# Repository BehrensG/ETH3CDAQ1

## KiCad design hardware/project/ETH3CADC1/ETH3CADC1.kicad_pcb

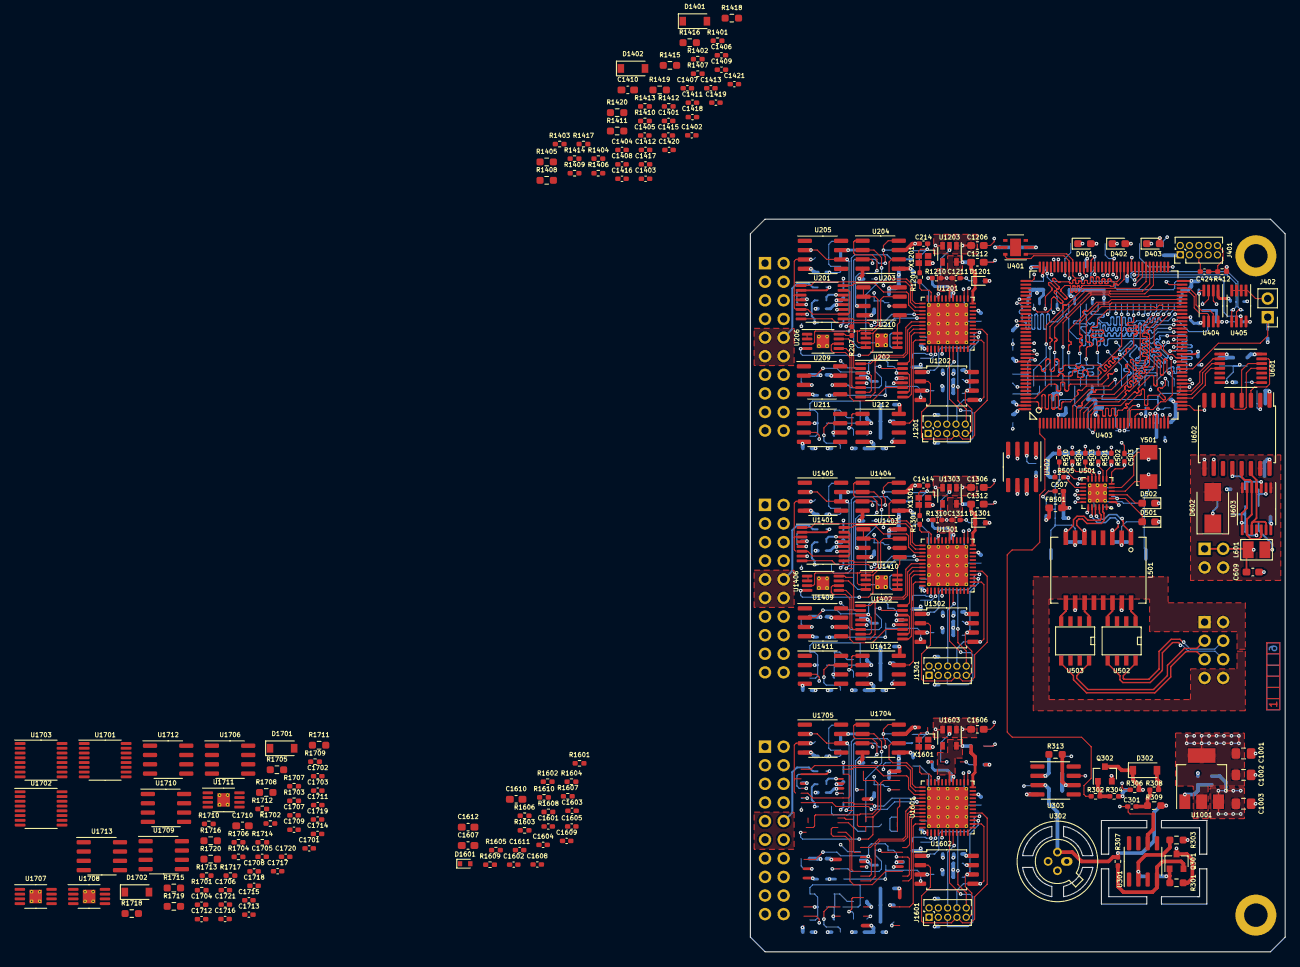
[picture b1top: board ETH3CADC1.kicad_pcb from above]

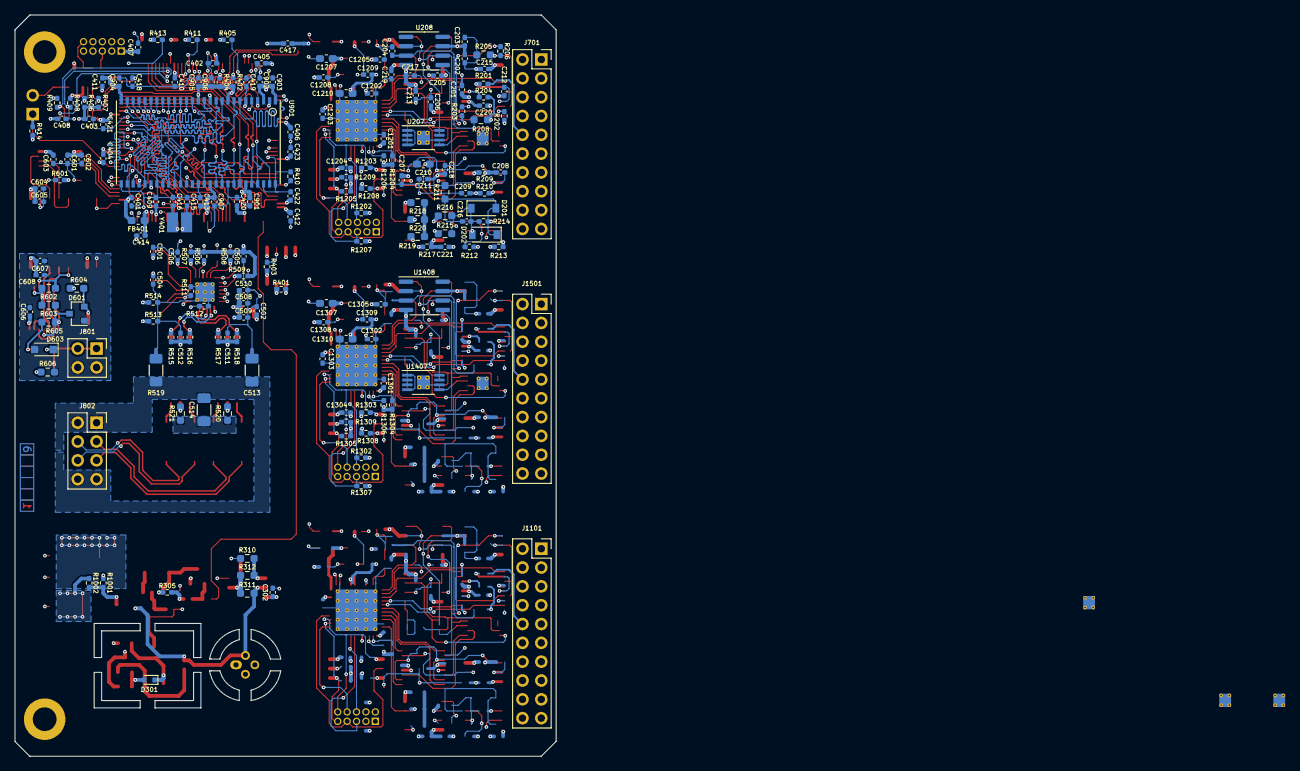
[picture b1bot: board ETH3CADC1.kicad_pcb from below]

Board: 6 copper layers, 73.0 x 100.0 mm, 408 parts (181 on the bottom side), 334 nets.

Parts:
C201, C202, C203, C204, C205, C206, C207, C208, C209, C211, C212, C213, C214, C215, C217, C218, C219, C220, C221, C301, C302, C401, C402, C403, C404, C405, C406, C407, C408, C409, C410, C411, C412, C413, C417, C421, C422, C423, C424, C502, C505, C508, C509, C510, C511, C512, C601, C603, C604, C606, C608, C901, C902, C903, C904, C905, C906, C907, C1201, C1202, C1203, C1204, C1205, C1208, C1209, C1211, C1301, C1302, C1303, C1304, C1305, C1308, C1309, C1311, C1401, C1402, C1403, C1404, C1405, C1406, C1407, C1408, C1409, C1411, C1412, C1413, C1414, C1415, C1417, C1418, C1419, C1420, C1421, C1601, C1602, C1603, C1604, C1605, C1608, C1609, C1611, C1701, C1702, C1703, C1704, C1705, C1706, C1707, C1708, C1709, C1711, C1712, C1713, C1714, C1715, C1717, C1718, C1719, C1720, C1721: 100n; C_0402_1005Metric_Pad0.74x0.62mm_HandSolder
C210, C1410, C1710: 2n2/SMD; C_0603_1608Metric_Pad1.08x0.95mm_HandSolder
C216, C1416, C1716: 33p; C_0402_1005Metric_Pad0.74x0.62mm_HandSolder
C414, C420, C506, C507, C602, C605, C607: 1u; C_0402_1005Metric_Pad0.74x0.62mm_HandSolder
C415, C416, C501, C504: 8p; C_0402_1005Metric_Pad0.74x0.62mm_HandSolder
C418, C419: 2u2; C_0402_1005Metric_Pad0.74x0.62mm_HandSolder
C503: 470p; C_0402_1005Metric_Pad0.74x0.62mm_HandSolder
C513, C514: 1n/1kV; C_1206_3216Metric_Pad1.33x1.80mm_HandSolder
C609: 47p; C_0603_1608Metric_Pad1.08x0.95mm_HandSolder
C1001: 10u/50V; C_0805_2012Metric_Pad1.18x1.45mm_HandSolder
C1002, C1003: 4u7/50V; C_0805_2012Metric_Pad1.18x1.45mm_HandSolder
C1206, C1207, C1210, C1212, C1306, C1307, C1310, C1312, C1606, C1607, C1610, C1612: 4u7; C_0603_1608Metric_Pad1.08x0.95mm_HandSolder
D201, D202, D302, D1401, D1402, D1701, D1702: BAV21W; D_SOD-123
D301: BZT585B15TQ-13; D_SOD-523
D401: BLUE; LED_0603_1608Metric_Pad1.05x0.95mm_HandSolder
D402, D502: GREEN; LED_0603_1608Metric_Pad1.05x0.95mm_HandSolder
D403: RED; LED_0603_1608Metric_Pad1.05x0.95mm_HandSolder
D501: YELLOW; LED_0603_1608Metric_Pad1.05x0.95mm_HandSolder
D601: BAV99; SOT-23
D602: SMBJ5.0A; D_SMB
D603: SD36C-01FTG; D_SOD-323_HandSoldering
D1201, D1301, D1601: CDBU0520; D_SOD-523
FB401, FB501: 742792031; L_0603_1608Metric_Pad1.05x0.95mm_HandSolder
H101, H102: MountingHole; MountingHole_3.2mm_M3_DIN965_Pad
J401: 20021111-00010T4LF; PinHeader_2x05_P1.27mm_Vertical
J402: Conn_02x01; PinHeader_1x02_P2.54mm_Vertical
J701, J1101, J1501: Conn_02x10_Odd_Even; PinSocket_2x10_P2.54mm_Vertical
J801: Conn_02x02_Odd_Even; PinSocket_2x02_P2.54mm_Vertical
J802: Conn_02x04_Odd_Even; PinSocket_2x04_P2.54mm_Vertical
J1201, J1301, J1601: Conn_02x05_Odd_Even; PinHeader_2x05_P1.27mm_Vertical
L501: 749010012A
L601: CW252016-R33G; CW252016
Q301: MMBTA55; SOT-23
Q302: BC847; SOT-23
R201, R202, R203, R204, R207, R410, R412, R414, R503, R506, R507, R508, R509, R511, R601, R1202, R1203, R1204, R1205, R1207, R1208, R1209, R1302, R1303, R1305, R1306, R1307, R1308, R1309, R1401, R1402, R1403, R1404, R1407, R1602, R1603, R1604, R1605, R1606, R1607, R1608, R1609, R1701, R1702, R1703, R1704, R1707: 10k; R_0402_1005Metric_Pad0.72x0.64mm_HandSolder
R205, R1405, R1705: 10M; R_0603_1608Metric_Pad0.98x0.95mm_HandSolder
R206, R305, R307, R1406, R1706: 0; R_0402_1005Metric_Pad0.72x0.64mm_HandSolder
R208, R218, R309, R1408, R1418, R1708, R1718: 62/.1%; R_0603_1608Metric_Pad0.98x0.95mm_HandSolder
R209, R210, R212, R213, R217, R1409, R1410, R1412, R1413, R1417, R1709, R1710, R1712, R1713, R1717: 10; R_0402_1005Metric_Pad0.72x0.64mm_HandSolder
R211, R1411, R1711: 12k/.05%; R_0603_1608Metric_Pad0.98x0.95mm_HandSolder
R214, R1414, R1714: 62k; R_0402_1005Metric_Pad0.72x0.64mm_HandSolder
R215, R1415, R1715: 620/.05%; R_0603_1608Metric_Pad0.98x0.95mm_HandSolder
R216, R220, R1416, R1420, R1716, R1720: 3k9/.05%; R_0603_1608Metric_Pad0.98x0.95mm_HandSolder
R219, R1419, R1719: 39k/.05%; R_0603_1608Metric_Pad0.98x0.95mm_HandSolder
R301, R303: 4k7/.1%; R_0603_1608Metric_Pad0.98x0.95mm_HandSolder
R302, R306: 120k; R_0402_1005Metric_Pad0.72x0.64mm_HandSolder
R304: 620k; R_0402_1005Metric_Pad0.72x0.64mm_HandSolder
R308: 12k; R_0402_1005Metric_Pad0.72x0.64mm_HandSolder
R310: 6k95/.05%; R_0603_1608Metric_Pad0.98x0.95mm_HandSolder
R311, R312: 3k01/.1%; R_0603_1608Metric_Pad0.98x0.95mm_HandSolder
R313: 0; R_0603_1608Metric_Pad0.98x0.95mm_HandSolder
R401, R1002: 120; R_0402_1005Metric_Pad0.72x0.64mm_HandSolder
R402, R404, R406, R407, R408, R409: 4k7; R_0402_1005Metric_Pad0.72x0.64mm_HandSolder
R403: 1k; R_0402_1005Metric_Pad0.72x0.64mm_HandSolder
R405, R413: 680; R_0402_1005Metric_Pad0.72x0.64mm_HandSolder
R411: 560; R_0402_1005Metric_Pad0.72x0.64mm_HandSolder
R501, R502, R504, R505: 33; R_0402_1005Metric_Pad0.72x0.64mm_HandSolder
R510: 1k5; R_0402_1005Metric_Pad0.72x0.64mm_HandSolder
R512: 12k1; R_0402_1005Metric_Pad0.72x0.64mm_HandSolder
R513, R514: 270; R_0402_1005Metric_Pad0.72x0.64mm_HandSolder
R515, R516, R517, R518: 49R9; R_0402_1005Metric_Pad0.72x0.64mm_HandSolder
R519: 1M/1kV; R_1206_3216Metric_Pad1.30x1.75mm_HandSolder
R520, R521: 75/1%; R_0603_1608Metric_Pad0.98x0.95mm_HandSolder
R602: 14k7; R_0603_1608Metric_Pad0.98x0.95mm_HandSolder
R603: 100; R_0603_1608Metric_Pad0.98x0.95mm_HandSolder
R604: 1k; R_0603_1608Metric_Pad0.98x0.95mm_HandSolder
R605: 47; R_0603_1608Metric_Pad0.98x0.95mm_HandSolder
R606: 51R1; R_0603_1608Metric_Pad0.98x0.95mm_HandSolder
R1001: 1k23; R_0402_1005Metric_Pad0.72x0.64mm_HandSolder
R1201, R1301, R1601: 22; R_0402_1005Metric_Pad0.72x0.64mm_HandSolder
R1206, R1304: NC; R_0402_1005Metric_Pad0.72x0.64mm_HandSolder
R1210, R1310, R1610: 100; R_0402_1005Metric_Pad0.72x0.64mm_HandSolder
U201, U1401, U1701, U1703: DG211; TSSOP-16_4.4x5mm_P0.65mm
U202, U1402, U1702: DG211B; TSSOP-16_4.4x5mm_P0.65mm
U203, U1403, U1704: OPA2192; SOIC-8_3.9x4.9mm_P1.27mm
U204, U1404, U1705: DG419DY; SOIC-8_3.9x4.9mm_P1.27mm
U205, U209, U1405, U1409, U1706, U1710: OPA140; SOIC-8_3.9x4.9mm_P1.27mm
U206, U1406, U1707: LT5400-100k-100k; MSOP-8-1EP_3x3mm_P0.65mm_EP1.73x1.85mm_ThermalVias
U207, U1407, U1708: LT5400-5k-1k; MSOP-8-1EP_3x3mm_P0.65mm_EP1.73x1.85mm_ThermalVias
U208, U303, U1408, U1709: OPA177; SOIC-8_3.9x4.9mm_P1.27mm
U210, U1410, U1711: LT5400-10k-10k; MSOP-8-1EP_3x3mm_P0.65mm_EP1.73x1.85mm_ThermalVias
U211, U1411, U1712: OPA192; SOIC-8_3.9x4.9mm_P1.27mm
U212, U1412, U1713: LM311; SOIC-8_3.9x4.9mm_P1.27mm
U301: LT1021-7; SOIC-8_3.9x4.9mm_P1.27mm
U302: LM399H; LMx99
U401: HDC1080; Texas_PWSON-N6
U402: MCP2551-I-SN; SOIC-8_3.9x4.9mm_P1.27mm
U403: STM32H743ZI; TQFP-144_20x20mm_P0.5mm
U404: PCA9517; MSOP-8_3x3mm_P0.65mm
U405: 24LC08B-E/MS; MSOP-8_3x3mm_P0.65mm
U501: LAN8742A; QFN-24-1EP_4x4mm_P0.5mm_EP2.6x2.6mm_ThermalVias
U502, U503: LC03-3.3; SO8E
U601: TXB0104PW; TSSOP-14_4.4x5mm_P0.65mm
U602: ADuM5402; SOIC-16W_7.5x10.3mm_P1.27mm
U603: 74AC125; TSSOP-14_4.4x5mm_P0.65mm
U901: MT48LC16M16A2P-6A; TSSOP-54
U1001: LM337_SOT223; SOT-223-3_TabPin2
U1201, U1301, U1601: ICE40UP5K-SG48ITR; QFN-48-1EP_7x7mm_P0.5mm_EP5.6x5.6mm_ThermalVias
U1202, U1302, U1602: W25Q32JVSS; SOIC-8_5.23x5.23mm_P1.27mm
U1203, U1303, U1603: AP2127K-1.2; SOT-23-5
X1201, X1301, X1601: ASAAIG-40.000MHZ; ASAAIG
Y401: NX3225GD-8MHZ; NX3225GD
Y501: NX5032GA-25.000M-LN-CD-1; NX5032GA

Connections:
+3.3VF: C219.1, C220.1, C221.1, C401.1, C402.1, C403.1, C404.1, C405.1, C406.1, C407.1, C408.1, C409.1, C410.1, C411.1, C412.1, C413.1, C417.1, C420.1, C421.1, C422.1, C423.1, C502.1, C505.1, C601.1, C602.1, C901.1, C902.1, C903.1, C904.1, C905.1, C906.1, C907.1, C1201.1, C1202.1, C1203.1, C1204.1, C1205.1, C1206.1, C1208.1, C1301.1, C1302.1, C1303.1, C1304.1, C1305.1, C1306.1, C1308.1, C1419.1, C1420.1, C1421.1, C1601.1, C1602.1, C1603.1, C1604.1, C1605.1, C1606.1, C1608.1, C1719.1, C1720.1, C1721.1, D401.2, D402.2, D403.2, D1201.2, D1301.2, D1601.2, FB401.2, FB501.2, J401.1, J701.15, J701.16, J1101.15, J1101.16, J1501.15, J1501.16, R218.1, R402.1, R404.1, R406.1, R407.1, R408.1, R409.1, R412.1, R414.2, R506.1, R507.1, R508.1, R509.1, R510.1, R601.1, R1202.1, R1203.1, R1204.1, R1205.1, R1206.1, R1207.1, R1208.1, R1209.1, R1302.1, R1303.1, R1304.1, R1305.1, R1306.1, R1307.1, R1308.1, R1309.1, R1418.1, R1602.1, R1603.1, R1604.1, R1605.1, R1606.1, R1607.1, R1608.1, R1609.1, R1718.1, U201.12, U202.12, U204.5, U212.8, U401.5, U403.6, U403.17, U403.30, U403.39, U403.52, U403.62, U403.72, U403.84, U403.95, U403.108, U403.121, U403.131, U403.143, U403.144, U404.1, U404.5, U404.8, U405.8, U501.9, U601.1, U901.1, U901.3, U901.9, U901.14, U901.27, U901.43, U901.49, U1201.1, U1201.22, U1201.33, U1202.8, U1203.1, U1203.3, U1301.1, U1301.22, U1301.33, U1302.8, U1303.1, U1303.3, U1401.12, U1402.12, U1404.5, U1412.8, U1601.1, U1601.22, U1601.33, U1602.8, U1603.1, U1603.3, U1701.12, U1702.12, U1705.5, U1713.8, X1201.4, X1301.4, X1601.4
+5V: C603.1, C604.1, C605.1, J701.18, J1101.18, J1501.18, U402.3, U601.14, U602.1
+5V_TRIG: C606.1, C607.1, C608.1, R604.1, U602.10, U602.16, U603.14
+10VRF: R203.2, R313.1, R1403.2, R1703.2
+18VF: C201.1, C202.1, C203.1, C205.1, C206.1, C207.1, C208.1, C1401.1, C1402.1, C1403.1, C1405.1, C1406.1, C1407.1, C1408.1, C1701.1, C1702.1, C1703.1, C1705.1, C1706.1, C1707.1, C1708.1, J701.20, J1101.20, J1501.20, R209.1, R212.1, R303.1, R1409.1, R1412.1, R1709.1, R1712.1, U201.13, U202.13, U203.4, U204.4, U205.7, U208.7, U302.3, U1401.13, U1402.13, U1403.4, U1404.4, U1405.7, U1408.7, U1701.13, U1702.13, U1704.4, U1705.4, U1706.7, U1709.7
-14VF: C209.1, C211.1, C212.1, C213.1, C214.1, C215.1, C217.1, C218.1, C302.2, C1003.1, C1409.1, C1411.1, C1412.1, C1413.1, C1414.1, C1415.1, C1417.1, C1418.1, C1709.1, C1711.1, C1712.1, C1713.1, C1714.1, C1715.1, C1717.1, C1718.1, Q301.3, Q302.2, R210.2, R213.2, R217.2, R301.2, R304.2, R305.1, R1002.1, R1410.2, R1413.2, R1417.2, R1710.2, R1713.2, R1717.2, U201.4, U202.4, U203.8, U204.7, U205.4, U208.4, U303.4, U1001.3, U1401.4, U1402.4, U1403.8, U1404.7, U1405.4, U1408.4, U1701.4, U1702.4, U1704.8, U1705.7, U1706.4, U1709.4
-18VF: C1001.1, C1002.1, J701.19, J1101.19, J1501.19, U302.4, U1001.2
/ADC 1/ADIN1: J701.9, J701.10, J701.11, J701.12, R201.2
/ADC 1/FGPA1_AD_ID: U202.16, U1201.44
/ADC 1/FGPA1_AD_IIN: U202.1, U1201.42
/ADC 1/FGPA1_AD_IRN: U202.8, U1201.43
/ADC 1/FGPA1_AD_IRP: U202.9, U1201.45
/ADC 1/FPGA1_MUX_ADIN: U201.1, U1201.38
/ADC 1/FPGA1_MUX_GND: U201.8, U1201.41
/ADC 1/FPGA1_MUX_N7V: U201.16, U1201.39
/ADC 1/FPGA1_MUX_P10V: U201.9, U1201.40
/ADC 1/VREF+: U203.7, U206.4, U210.1, U210.2
/ADC 1/VREF-: U203.1, U203.2, U206.3, U210.3, U210.4
/ADC 1/VREF_N7V_LPF: C301.1, R204.2, R208.2, R308.1, R309.1, R1404.2, R1408.2, R1704.2, R1708.2
/ADC 2/ADIN2: J1501.9, J1501.10, J1501.11, J1501.12, R1401.2
/ADC 2/FGPA2_AD_ID: U1301.44, U1402.16
/ADC 2/FGPA2_AD_IIN: U1301.42, U1402.1
/ADC 2/FGPA2_AD_IRN: U1301.43, U1402.8
/ADC 2/FGPA2_AD_IRP: U1301.45, U1402.9
/ADC 2/FPGA2_MUX_ADIN: U1301.38, U1401.1
/ADC 2/FPGA2_MUX_GND: U1301.41, U1401.8
/ADC 2/FPGA2_MUX_N7V: U1301.39, U1401.16
/ADC 2/FPGA2_MUX_P10V: U1301.40, U1401.9
/ADC 2/VREF+: U1403.7, U1406.4, U1410.1, U1410.2
/ADC 2/VREF-: U1403.1, U1403.2, U1406.3, U1410.3, U1410.4
/ADC 3/ADIN3: J1101.9, J1101.10, J1101.11, J1101.12, R1701.2
/ADC 3/FGPA3_AD_ID: U1601.44, U1702.16
/ADC 3/FGPA3_AD_IIN: U1601.42, U1702.1
/ADC 3/FGPA3_AD_IRN: U1601.43, U1702.8
/ADC 3/FGPA3_AD_IRP: U1601.45, U1702.9
/ADC 3/FPGA3_MUX_ADIN: U1601.38, U1703.1
/ADC 3/FPGA3_MUX_GND: U1601.41, U1703.8
/ADC 3/FPGA3_MUX_N7V: U1601.39, U1703.16
/ADC 3/FPGA3_MUX_P10V: U1601.40, U1703.9
/ADC 3/VREF+: U1704.7, U1707.4, U1711.1, U1711.2
/ADC 3/VREF-: U1704.1, U1704.2, U1707.3, U1711.3, U1711.4
/CH1 Connector/CANH: J701.5, J1101.5, J1501.5, R401.1, U402.7
/CH1 Connector/CANL: J701.6, J1101.6, J1501.6, R401.2, U402.6
/CH1 Connector/I2C_SCL: J701.2, J1101.2, J1501.2, R406.2, U404.2
/CH1 Connector/I2C_SDA: J701.4, J1101.4, J1501.4, R407.2, U404.3
/Connector/EXT_TRIG: C609.1, D603.1, J801.1, J801.2, L601.1
/Connector/RX+: J802.3, U503.8
/Connector/RX-: J802.5, U503.5
/Connector/TX+: J802.4, U502.8
/Connector/TX-: J802.6, U502.5
/Ethernet/ETH_RXN: L501.8, R518.2, U501.22
/Ethernet/ETH_RXP: L501.6, R517.2, U501.23
/Ethernet/ETH_TXN: L501.3, R516.2, U501.20
/Ethernet/ETH_TXP: L501.1, R515.2, U501.21
/Ethernet/MODE0: R501.1, R506.2, U501.8
/Ethernet/MODE1: R502.1, R507.2, U501.7
/Ethernet/MODE2: R504.1, R508.2, U501.11
/Ethernet/NRST: C424.1, J401.10, R412.2, U403.25, U501.15
/Ethernet/REFCLK0: R505.1, R509.2, U501.14
/Ethernet/REF_CLK: R505.2, U403.35
/Ethernet/RMII_CRS_DV: R504.2, U403.43
/Ethernet/RMII_MDC: U403.27, U501.13
/Ethernet/RMII_MDIO: R510.2, U403.36, U501.12
/Ethernet/RMII_RXD0: R501.2, U403.44
/Ethernet/RMII_RXD1: R502.2, U403.45
/Ethernet/RMII_TXD0: U403.128, U501.17
/Ethernet/RMII_TXD1: U403.129, U501.18
/Ethernet/RMII_TXEN: U403.126, U501.16
/FPGA 1/ADC_COMP1: R220.2, U212.7, U1201.47
/FPGA 1/CODE1: R1204.2, U1201.2
/FPGA 1/CODE2: R1206.2, U1201.3
/FPGA 1/FGPA1_AD_VRH: U204.6, U1201.37
/FPGA 1/FGPA1_MISO: U1201.20, U1301.19
/FPGA 1/FGPA1_MOSI: U403.113, U1201.19
/FPGA 1/FGPA1_SCLK: U403.111, U1201.21, U1301.21, U1601.21
/FPGA 1/FGPA1_nSS: U403.110, U1201.23, U1301.23, U1601.23
/FPGA 1/FPGA1_UART6_RX: U403.97, U1201.26
/FPGA 1/FPGA1_UART6_TX: U403.96, U1201.25
/FPGA 1/FPGA_CLK: R1201.1, U1201.35
/FPGA 1/iCE_CDONE: J1201.5, R1207.2, U1201.7
/FPGA 1/iCE_CRESET: J1201.6, R1202.2, U1201.8
/FPGA 1/iCE_MISO: J1201.8, U1201.14, U1202.5
/FPGA 1/iCE_MOSI: J1201.7, U1201.17, U1202.2
/FPGA 1/iCE_SCK: J1201.9, R1205.2, U1201.15, U1202.6
/FPGA 1/iCE_SSn: J1201.10, R1203.2, U1201.16, U1202.1
/FPGA 2/ADC_COMP2: R1420.2, U1301.47, U1412.7
/FPGA 2/CODE1: R1304.2, U1301.2
/FPGA 2/CODE2: R1306.2, U1301.3
/FPGA 2/FGPA2_AD_VRH: U1301.37, U1404.6
/FPGA 2/FGPA2_MISO: U1301.20, U1601.19
/FPGA 2/FPGA2_UART2_RX: U403.122, U1301.26
/FPGA 2/FPGA2_UART2_TX: U403.119, U1301.25
/FPGA 2/FPGA_CLK: R1301.1, U1301.35
/FPGA 2/iCE_CDONE: J1301.5, R1307.2, U1301.7
/FPGA 2/iCE_CRESET: J1301.6, R1302.2, U1301.8
/FPGA 2/iCE_MISO: J1301.8, U1301.14, U1302.5
/FPGA 2/iCE_MOSI: J1301.7, U1301.17, U1302.2
/FPGA 2/iCE_SCK: J1301.9, R1305.2, U1301.15, U1302.6
/FPGA 2/iCE_SSn: J1301.10, R1303.2, U1301.16, U1302.1
/FPGA 3/ADC_COMP3: R1720.2, U1601.47, U1713.7
/FPGA 3/CODE1: R1604.2, U1601.2
/FPGA 3/CODE2: R1606.2, U1601.3
/FPGA 3/FGPA3_AD_VRH: U1601.37, U1705.6
/FPGA 3/FGPA3_MISO: U403.112, U1601.20
/FPGA 3/FPGA3_UART2_RX: U403.133, U1601.26
/FPGA 3/FPGA3_UART2_TX: U403.134, U1601.25
/FPGA 3/FPGA_CLK: R1601.1, U1601.35
/FPGA 3/iCE_CDONE: J1601.5, R1607.2, U1601.7
/FPGA 3/iCE_CRESET: J1601.6, R1602.2, U1601.8
/FPGA 3/iCE_MISO: J1601.8, U1601.14, U1602.5
/FPGA 3/iCE_MOSI: J1601.7, U1601.17, U1602.2
/FPGA 3/iCE_SCK: J1601.9, R1605.2, U1601.15, U1602.6
/FPGA 3/iCE_SSn: J1601.10, R1603.2, U1601.16, U1602.1
/MCU/A0: U403.10, U901.23
/MCU/A1: U403.11, U901.24
/MCU/A2: U403.12, U901.25
/MCU/A3: U403.13, U901.26
/MCU/A4: U403.14, U901.29
/MCU/A5: U403.15, U901.30
/MCU/A6: U403.50, U901.31
/MCU/A7: U403.53, U901.32
/MCU/A8: U403.54, U901.33
/MCU/A9: U403.55, U901.34
/MCU/A10: U403.56, U901.22
/MCU/A11: U403.57, U901.35
/MCU/A12: U403.87, U901.36
/MCU/BA0: U403.89, U901.20
/MCU/BA1: U403.90, U901.21
/MCU/CAN_RX: U402.4, U403.103
/MCU/CAN_TX: U402.1, U403.104
/MCU/CKE: U403.135, U901.37
/MCU/CLK: U403.93, U901.38
/MCU/D0: U403.85, U901.2
/MCU/D1: U403.86, U901.4
/MCU/D2: U403.114, U901.5
/MCU/D3: U403.115, U901.7
/MCU/D4: U403.58, U901.8
/MCU/D5: U403.59, U901.10
/MCU/D6: U403.60, U901.11
/MCU/D7: U403.63, U901.13
/MCU/D8: U403.64, U901.42
/MCU/D9: U403.65, U901.44
/MCU/D10: U403.66, U901.45
/MCU/D11: U403.67, U901.47
/MCU/D12: U403.68, U901.48
/MCU/D13: U403.77, U901.50
/MCU/D14: U403.78, U901.51
/MCU/D15: U403.79, U901.53
/MCU/EEPROM_SCL: R409.2, U403.81, U405.6
/MCU/EEPROM_SDA: R408.2, U403.82, U405.5
/MCU/EEPROM_WP: U403.80, U405.7
/MCU/LDQM: U403.141, U901.15
/MCU/MCU_AD_RFS: R302.2, U403.1
/MCU/MCU_VDDA: C414.1, FB401.1, U403.32, U403.33
/MCU/MODULE_SCL: U403.69, U404.6
/MCU/MODULE_SDA: U403.70, U404.7
/MCU/SENS_SCL: R402.2, U401.6, U403.100
/MCU/SENS_SDA: R404.2, U401.1, U403.99
/MCU/TCK_SWCLK: J401.4, U403.109
/MCU/TMS_SWDIO: J401.2, U403.105
/MCU/TRIG_EN: U403.42, U601.2
/MCU/TRIG_IN: U403.40, U601.4
/MCU/TRIG_OUT: U403.41, U601.3
/MCU/UDQM: U403.142, U901.39
/MCU/~CAS: U403.132, U901.17
/MCU/~CS: U403.136, U901.19
/MCU/~RAS: U403.49, U901.18
/MCU/~WE: U403.26, U901.16
/Trigger/EXT_TRIG_SIGN: R602.1, U602.12, U603.3
/Trigger/TRIG_OUT_EN: U602.14, U603.4, U603.10, U603.13
/Trigger/TRIG_OUT_SIGN: U602.13, U603.5, U603.9, U603.12
AGNDF: C201.2, C202.2, C203.2, C204.2, C205.2, C206.2, C207.2, C208.2, C209.2, C211.2, C212.2, C213.2, C214.2, C215.2, C217.2, C218.2, C219.2, C220.2, C301.2, C302.1, C401.2, C402.2, C403.2, C404.2, C405.2, C406.2, C407.2, C408.2, C409.2, C410.2, C411.2, C412.2, C413.2, C414.2, C415.2, C416.2, C417.2, C418.2, C419.2, C420.2, C421.2, C422.2, C423.2, C424.2, C501.2, C502.2, C503.2, C504.2, C505.2, C506.2, C507.2, C508.2, C509.2, C510.2, C511.2, C512.2, C513.2, C601.2, C602.2, C603.2, C604.2, C605.2, C901.2, C902.2, C903.2, C904.2, C905.2, C906.2, C907.2, C1001.2, C1002.2, C1003.2, C1201.2, C1202.2, C1203.2, C1204.2, C1205.2, C1206.2, C1207.2, C1208.2, C1209.2, C1210.2, C1211.2, C1212.2, C1301.2, C1302.2, C1303.2, C1304.2, C1305.2, C1306.2, C1307.2, C1308.2, C1309.2, C1310.2, C1311.2, C1312.2, C1401.2, C1402.2, C1403.2, C1404.2, C1405.2, C1406.2, C1407.2, C1408.2, C1409.2, C1411.2, C1412.2, C1413.2, C1414.2, C1415.2, C1417.2, C1418.2, C1419.2, C1420.2, C1601.2, C1602.2, C1603.2, C1604.2, C1605.2, C1606.2, C1607.2, C1608.2, C1609.2, C1610.2, C1611.2, C1612.2, C1701.2, C1702.2, C1703.2, C1704.2, C1705.2, C1706.2, C1707.2, C1708.2, C1709.2, C1711.2, C1712.2, C1713.2, C1714.2, C1715.2, C1717.2, C1718.2, C1719.2, C1720.2, J401.3, J401.5, J402.2, J701.1, J701.3, J701.7, J701.8, J701.13, J701.14, J1101.1, J1101.3, J1101.7, J1101.8, J1101.13, J1101.14, J1201.2, J1301.2, J1501.1, J1501.3, J1501.7, J1501.8, J1501.13, J1501.14, J1601.2, R202.2, R205.2, R215.2, R306.2, R310.2, R403.2, R410.2, R503.2, R511.2, R512.1, R513.2, R514.2, R519.2, R1001.2, R1402.2, R1405.2, R1415.2, R1702.2, R1705.2, R1715.2, U201.5, U202.5, U203.6, U204.3, U206.9, U207.6, U207.9, U209.3, U210.9, U211.3, U212.1, U301.6, U302.1, U303.7, U401.2, U402.2, U403.16, U403.31, U403.38, U403.51, U403.61, U403.83, U403.94, U403.107, U403.120, U403.130, U404.4, U405.1, U405.2, U405.3, U405.4, U501.25, U601.7, U602.2, U602.8, U901.6, U901.12, U901.28, U901.41, U901.46, U901.52, U901.54, U1201.49, U1202.4, U1203.2, U1301.49, U1302.4, U1303.2, U1401.5, U1402.5, U1403.6, U1404.3, U1406.9, U1407.6, U1407.9, U1409.3, U1410.9, U1411.3, U1412.1, U1601.49, U1602.4, U1603.2, U1701.5, U1702.5, U1704.6, U1705.3, U1707.9, U1708.6, U1708.9, U1710.3, U1711.9, U1712.3, U1713.1, X1201.2, X1301.2, X1601.2
Earth: C513.1, C514.2, J802.1, J802.2, J802.7, J802.8, R519.1
GND_TRIG: C606.2, C607.2, C608.2, D601.1, D602.2, D603.2, J801.3, J801.4, R606.2, U602.9, U602.15, U603.1, U603.7
unnamed: C204.1, R208.1, U208.3
unnamed: C210.1, R211.2, U202.15, U209.6
unnamed: C210.2, U202.3, U202.7, U202.10, U202.14, U209.2
unnamed: C216.1, D201.1, D202.2, R214.1, R216.2, U211.6
unnamed: C216.2, D201.2, D202.1, R211.1, R214.2, U211.2
unnamed: C221.2, R217.1, U212.4
unnamed: C415.1, U403.23, Y401.1
unnamed: C416.1, U403.24, Y401.2
unnamed: C418.1, U403.71
unnamed: C419.1, U403.106
unnamed: C501.1, U501.5, Y501.2
unnamed: C503.1, C506.1, U501.6
unnamed: C504.1, U501.4, Y501.1
unnamed: C514.1, R520.2, R521.2
unnamed: C609.2, R606.1
unnamed: C1207.1, C1211.1, R1210.2, U1201.5, U1201.30, U1203.5
unnamed: C1209.1, C1210.1, R1210.1, U1201.29
unnamed: C1212.1, D1201.1, U1201.24
unnamed: C1307.1, C1311.1, R1310.2, U1301.5, U1301.30, U1303.5
unnamed: C1309.1, C1310.1, R1310.1, U1301.29
unnamed: C1312.1, D1301.1, U1301.24
unnamed: C1404.1, R1408.1, U1408.3
unnamed: C1410.1, R1411.2, U1402.15, U1409.6
unnamed: C1410.2, U1402.3, U1402.7, U1402.10, U1402.14, U1409.2
unnamed: C1416.1, D1401.1, D1402.2, R1414.1, R1416.2, U1411.6
unnamed: C1416.2, D1401.2, D1402.1, R1411.1, R1414.2, U1411.2
unnamed: C1421.2, R1417.1, U1412.4
unnamed: C1607.1, C1611.1, R1610.2, U1601.5, U1601.30, U1603.5
unnamed: C1609.1, C1610.1, R1610.1, U1601.29
unnamed: C1612.1, D1601.1, U1601.24
unnamed: C1704.1, R1708.1, U1709.3
unnamed: C1710.1, R1711.2, U1702.15, U1710.6
unnamed: C1710.2, U1702.3, U1702.7, U1702.10, U1702.14, U1710.2
unnamed: C1716.1, D1701.1, D1702.2, R1714.1, R1716.2, U1712.6
unnamed: C1716.2, D1701.2, D1702.1, R1711.1, R1714.2, U1712.2
unnamed: C1721.2, R1717.1, U1713.4
unnamed: D301.1, R303.2, U301.2
unnamed: D301.2, Q301.1, R301.1
unnamed: D302.1, Q302.3, R305.2, R306.1
unnamed: D302.2, R308.2
unnamed: D401.1, R405.2
unnamed: D402.1, R411.2
unnamed: D403.1, R413.2
unnamed: D501.1, R513.1
unnamed: D501.2, R511.1, U501.2
unnamed: D502.1, R514.1
unnamed: D502.2, U501.3
unnamed: D601.2, D602.1, R604.2
unnamed: D601.3, R603.2, R605.1, U603.6, U603.8, U603.11
unnamed: J402.1, R414.1, U403.48
unnamed: L501.9, U503.4
unnamed: L501.10, R520.1
unnamed: L501.11, U503.1
unnamed: L501.14, U502.4
unnamed: L501.15, R521.1
unnamed: L501.16, U502.1
unnamed: L601.2, R605.2
unnamed: Q301.2, R307.2, U301.4
unnamed: Q302.1, R302.1, R304.1
unnamed: R201.1, U201.2
unnamed: R202.1, U201.7
unnamed: R203.1, U201.11
unnamed: R204.1, U201.14
unnamed: R205.1, R206.2, U201.3, U201.6, U201.10, U201.15, U205.3
unnamed: R206.1, R207.2, U205.2, U205.6
unnamed: R207.1, U206.8
unnamed: R209.2, U209.7
unnamed: R210.1, U209.4
unnamed: R212.2, U211.7
unnamed: R213.1, U211.4
unnamed: R215.1, U212.3
unnamed: R216.1, U212.2
unnamed: R218.2, R219.1, R220.1
unnamed: R219.2, U212.5
unnamed: R307.1, R309.2, R311.2, U302.2, U303.3
unnamed: R310.1, R312.2, U303.2
unnamed: R311.1, R312.1, R313.2, U303.6
unnamed: R403.1, U402.8
unnamed: R405.1, U403.101
unnamed: R410.1, U403.138
unnamed: R411.1, U403.88
unnamed: R413.1, U403.73
unnamed: R503.1, U501.10
unnamed: R512.2, U501.24
unnamed: R601.2, U601.8
unnamed: R602.2, R603.1, U603.2
unnamed: R1001.1, R1002.2, U1001.1
unnamed: R1201.2, X1201.3
unnamed: R1208.2, U1202.3
unnamed: R1209.2, U1202.7
unnamed: R1301.2, X1301.3
unnamed: R1308.2, U1302.3
unnamed: R1309.2, U1302.7
unnamed: R1401.1, U1401.2
unnamed: R1402.1, U1401.7
unnamed: R1403.1, U1401.11
unnamed: R1404.1, U1401.14
unnamed: R1405.1, R1406.2, U1401.3, U1401.6, U1401.10, U1401.15, U1405.3
unnamed: R1406.1, R1407.2, U1405.2, U1405.6
unnamed: R1407.1, U1406.8
unnamed: R1409.2, U1409.7
unnamed: R1410.1, U1409.4
unnamed: R1412.2, U1411.7
unnamed: R1413.1, U1411.4
unnamed: R1415.1, U1412.3
unnamed: R1416.1, U1412.2
unnamed: R1418.2, R1419.1, R1420.1
unnamed: R1419.2, U1412.5
unnamed: R1601.2, X1601.3
unnamed: R1608.2, U1602.3
unnamed: R1609.2, U1602.7
unnamed: R1701.1, U1703.2
unnamed: R1702.1, U1703.7
unnamed: R1703.1, U1703.11
unnamed: R1704.1, U1703.14
unnamed: R1705.1, R1706.2, U1703.3, U1703.6, U1703.10, U1703.15, U1706.3
unnamed: R1706.1, R1707.2, U1706.2, U1706.6
unnamed: R1707.1, U1707.8
unnamed: R1709.2, U1710.7
unnamed: R1710.1, U1710.4
unnamed: R1712.2, U1712.7
unnamed: R1713.1, U1712.4
unnamed: R1715.1, U1713.3
unnamed: R1716.1, U1713.2
unnamed: R1718.2, R1719.1, R1720.1
unnamed: R1719.2, U1713.5
unnamed: U202.2, U206.7
unnamed: U202.6, U206.5
unnamed: U202.11, U206.6
unnamed: U203.3, U204.1
unnamed: U203.5, U210.5, U210.6, U210.7, U210.8
unnamed: U204.2, U207.7, U207.8
unnamed: U204.8, U207.5, U208.2, U208.6
unnamed: U206.1, U206.2
unnamed: U207.1, U207.4
unnamed: U207.2, U207.3
unnamed: U601.11, U602.5
unnamed: U601.12, U602.4
unnamed: U601.13, U602.3
unnamed: U1402.2, U1406.7
unnamed: U1402.6, U1406.5
unnamed: U1402.11, U1406.6
unnamed: U1403.3, U1404.1
unnamed: U1403.5, U1410.5, U1410.6, U1410.7, U1410.8
unnamed: U1404.2, U1407.7, U1407.8
unnamed: U1404.8, U1407.5, U1408.2, U1408.6
unnamed: U1406.1, U1406.2
unnamed: U1407.1, U1407.4
unnamed: U1407.2, U1407.3
unnamed: U1702.2, U1707.7
unnamed: U1702.6, U1707.5
unnamed: U1702.11, U1707.6
unnamed: U1704.3, U1705.1
unnamed: U1704.5, U1711.5, U1711.6, U1711.7, U1711.8
unnamed: U1705.2, U1708.7, U1708.8
unnamed: U1705.8, U1708.5, U1709.2, U1709.6
unnamed: U1707.1, U1707.2
unnamed: U1708.1, U1708.4
unnamed: U1708.2, U1708.3
VCCQ: C507.1, C508.1, C509.1, C510.1, C511.1, C512.1, FB501.1, L501.2, L501.7, R515.1, R516.1, R517.1, R518.1, U501.1, U501.19

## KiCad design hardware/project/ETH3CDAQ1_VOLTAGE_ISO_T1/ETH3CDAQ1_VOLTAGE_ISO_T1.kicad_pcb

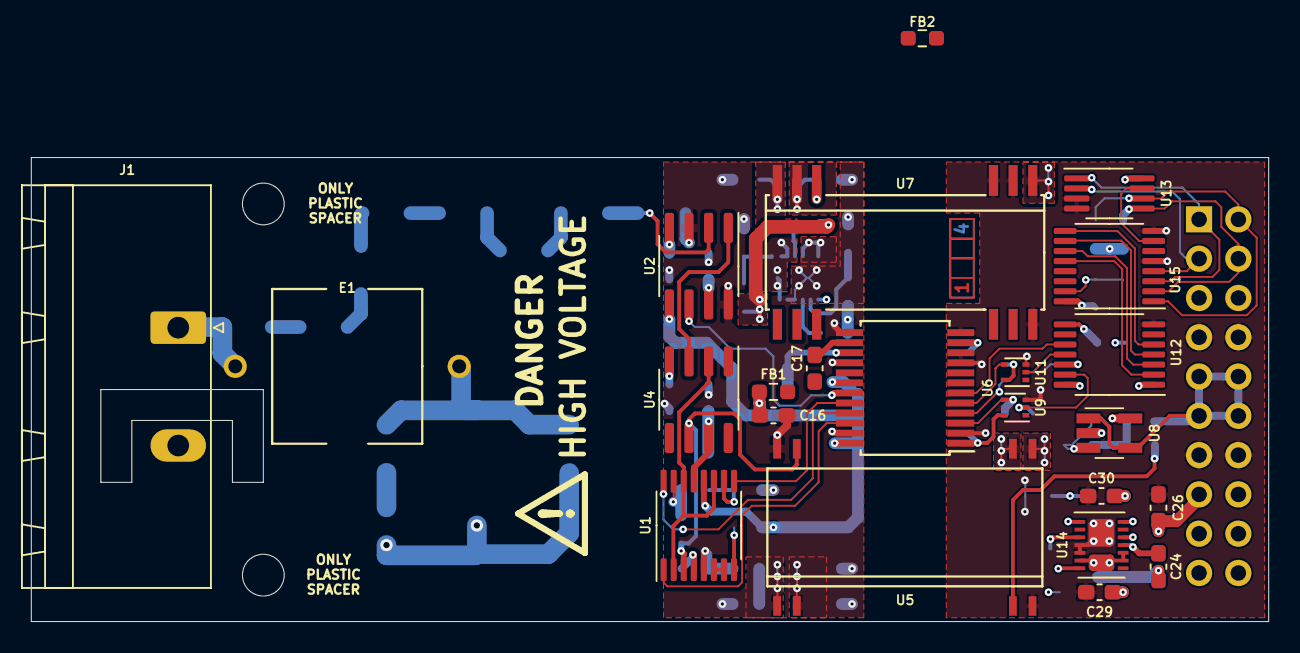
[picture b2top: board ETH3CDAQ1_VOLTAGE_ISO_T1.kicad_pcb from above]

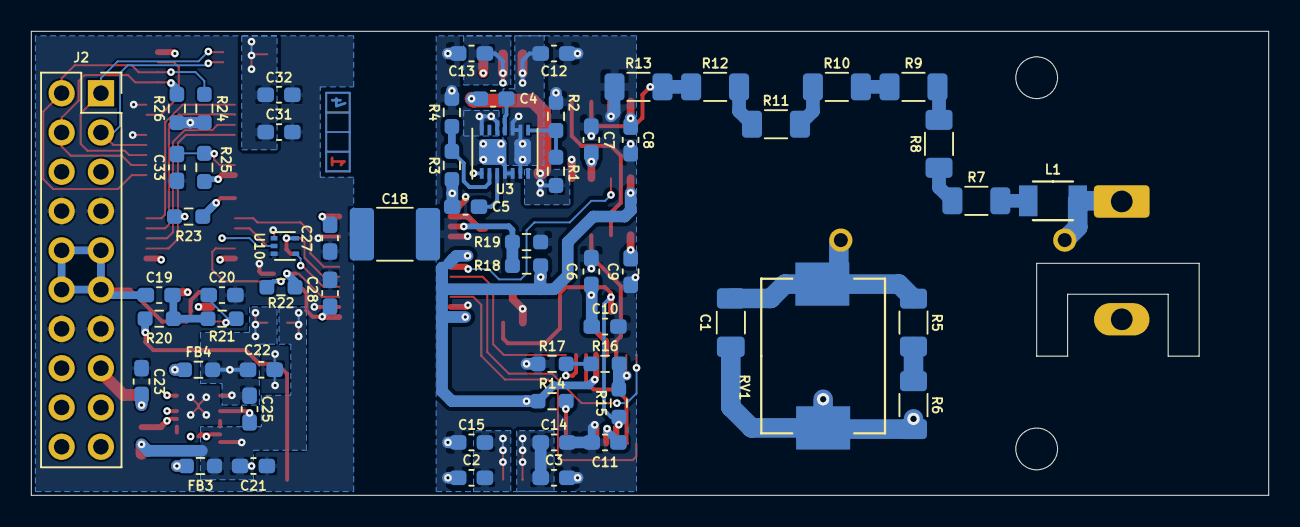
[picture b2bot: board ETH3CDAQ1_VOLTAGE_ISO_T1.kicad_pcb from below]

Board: 4 copper layers, 80.0 x 30.0 mm, 86 parts (60 on the bottom side), 65 nets.

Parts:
C1: 10n; C_1206_3216Metric_Pad1.33x1.80mm_HandSolder
C2, C3, C14, C15, C16, C21, C22, C23, C27, C31: 10u; C_0603_1608Metric_Pad1.08x0.95mm_HandSolder
C4, C5, C24, C25: 10n; C_0603_1608Metric_Pad1.08x0.95mm_HandSolder
C6, C7, C8, C9, C10, C11, C17, C26, C28, C32, C33: 100n; C_0603_1608Metric_Pad1.08x0.95mm_HandSolder
C12, C13, C29, C30: 2u2; C_0603_1608Metric_Pad1.08x0.95mm_HandSolder
C18: C; C_1812_4532Metric_Pad1.57x3.40mm_HandSolder
C19: 1n; C_0603_1608Metric_Pad1.08x0.95mm_HandSolder
C20: 220p; C_0603_1608Metric_Pad1.08x0.95mm_HandSolder
E1: CG3-1.5L; GDT
FB1, FB2: FB; R_0603_1608Metric_Pad0.98x0.95mm_HandSolder
FB3, FB4: Ferrite_Bead_Small; R_0603_1608Metric_Pad0.98x0.95mm_HandSolder
H1, H2: MountingHole; MountingHole_2.7mm_M2.5_DIN965
J1: GMSTB2,5/2-GF-7,62; PhoenixContact_GMSTB_2,5_2-GF-7,62_1x02_P7.62mm_Horizontal_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
J2: Conn_02x10_Odd_Even; PinSocket_2x10_P2.54mm_Vertical
L1: NLFV32T-100K-EF; NLV32
R1, R3: 536k; R_0603_1608Metric_Pad0.98x0.95mm_HandSolder
R2, R4: 49k3; R_0603_1608Metric_Pad0.98x0.95mm_HandSolder
R5, R6: 1M; R_1206_3216Metric_Pad1.30x1.75mm_HandSolder
R7: 6k19; R_1206_3216Metric_Pad1.30x1.75mm_HandSolder
R8, R9, R10, R11: 2M2; R_1206_3216Metric_Pad1.30x1.75mm_HandSolder
R12: 1M1; R_1206_3216Metric_Pad1.30x1.75mm_HandSolder
R13: 100k; R_1206_3216Metric_Pad1.30x1.75mm_HandSolder
R14, R19, R23, R25: 10k; R_0603_1608Metric_Pad0.98x0.95mm_HandSolder
R15: 180k/0.05%; R_0603_1608Metric_Pad0.98x0.95mm_HandSolder
R16: 18k/0.05%; R_0603_1608Metric_Pad0.98x0.95mm_HandSolder
R17: 2k/0.05%; R_0603_1608Metric_Pad0.98x0.95mm_HandSolder
R18: 30k9; R_0603_1608Metric_Pad0.98x0.95mm_HandSolder
R20: 4k75; R_0603_1608Metric_Pad0.98x0.95mm_HandSolder
R21: 9k76; R_0603_1608Metric_Pad0.98x0.95mm_HandSolder
R22: 0; R_0603_1608Metric_Pad0.98x0.95mm_HandSolder
R24, R26: 4k7; R_0603_1608Metric_Pad0.98x0.95mm_HandSolder
RV1: B72660M0301; 4032
SYM1: SYM_Flash_Large; Symbol_HighVoltage_Type2_CopperTop_VerySmall
U1: DG211; TSSOP-16_4.4x5mm_P0.65mm
U2: DG419xY; SOIC-8_3.9x4.9mm_P1.27mm
U3: LT3032; Linear_DE14MA
U4: OPA140; SOIC-8_3.9x4.9mm_P1.27mm
U5: ISO124; DVA
U6: ADuM5410; SSOP-24_5.3x8.2mm_P0.65mm
U7: DCP020515DU; DVB
U8: OPA237_SOT23; SOT-23-5_HandSoldering
U9, U10, U11: 74LVC1GU04DRL; SOT-553
U12: TXB0104PW; TSSOP-14_4.4x5mm_P0.65mm
U13: 24LC08B-E/MS; MSOP-8_3x3mm_P0.65mm
U14: LT3032-15; Linear_DE14MA
U15: PCA9557PW; TSSOP-16_4.4x5mm_P0.65mm

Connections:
+3V3: C23.1, C26.1, J2.15, J2.16, R23.1, R24.1, R25.1, R26.1, U12.1, U13.8, U15.16
+5V: C27.1, C28.1, C31.1, C32.1, J2.18, U6.1, U6.11, U7.1, U9.5, U10.5, U11.5, U12.14
+5VF: C16.1, FB1.2, R14.2, R18.1, U1.12, U2.5, U6.18, U6.24
+15V: C22.1, C25.1, FB4.2, U5.9, U8.5, U14.1
+15VF: C3.1, C5.1, C6.1, C8.1, C10.1, C14.1, R3.1, U1.13, U2.4, U3.1, U4.7, U5.1
+18V: C30.1, FB4.1, J2.20, U14.12, U14.14
-15V: C21.1, C24.1, FB3.2, U5.10, U8.2, U14.7
-15VF: C2.1, C4.1, C7.1, C9.1, C11.1, C15.1, R1.1, U1.4, U2.7, U3.7, U4.4, U5.2
-18V: C29.1, FB3.1, J2.19, U14.6, U14.9, U14.10
/A0: J2.1, U13.1, U15.3
/A1: J2.3, U13.2, U15.4
/AOUT: C19.1, J2.9, J2.10, J2.11, J2.12, U8.1, U8.4
/AZ: U2.6, U6.19
/G1: U1.1, U6.22
/G10: U1.16, U6.21
/G100: U1.9, U6.20
/IO2: U12.5, U15.9
/IO3: U12.4, U15.10
/IO4: U12.3, U15.11
/IO5: U12.2, U15.12
/IO_AZ: U6.6, U12.10
/IO_G1: R22.2, U6.3, U9.4
/IO_G10: U6.4, U10.4
/IO_G100: U6.5, U11.4
/NADJ: R1.2, R2.1, U3.8
/PADJ: R3.2, R4.1, U3.2
/SCL: J2.2, R24.2, U13.6, U15.1
/SDA: J2.4, R26.2, U13.5, U15.2
/WP: U13.7, U15.7
AGNDF: C1.2, C2.2, C3.2, C6.2, C7.2, C8.2, C9.2, C10.2, C11.2, C12.2, C13.2, C14.2, C15.2, C16.2, C18.2, FB2.2, J1.2, R2.2, R4.2, R6.2, R13.1, R17.2, R19.2, RV1.2, U1.5, U2.3, U2.8, U3.4, U3.5, U5.16, U6.13, U6.16, U6.23, U7.12
GND: C18.1, C20.2, C21.2, C22.2, C23.2, C26.2, C27.2, C28.2, C29.2, C30.2, C31.2, C32.2, C33.2, J2.7, J2.8, J2.13, J2.14, U5.8, U6.2, U6.9, U6.10, U6.12, U7.2, U7.3, U7.28, U9.3, U10.3, U11.3, U12.7, U13.3, U13.4, U14.4, U14.5, U15.5, U15.8
unnamed: C1.1, E1.2, R5.1, RV1.1
unnamed: C4.2, U3.11
unnamed: C5.2, U3.3
unnamed: C17.1, FB1.1, U6.14
unnamed: C17.2, FB2.1
unnamed: C19.2, R20.1, R21.2
unnamed: C20.1, R21.1, U8.3
unnamed: C24.2, U14.11
unnamed: C25.2, U14.3
unnamed: C33.1, R25.2, U15.15
unnamed: E1.1, J1.1, L1.1
unnamed: L1.2, R7.2
unnamed: R5.2, R6.1
unnamed: R7.1, R8.2
unnamed: R8.1, R9.2
unnamed: R10.1, R11.2
unnamed: R9.1, R10.2
unnamed: R11.1, R12.2
unnamed: R12.1, R13.2, U2.2
unnamed: R14.1, U1.8
unnamed: R15.1, U1.3, U4.6, U5.15
unnamed: R15.2, R16.1, U1.15
unnamed: R16.2, R17.1, U1.10
unnamed: R18.2, R19.1, U6.15
unnamed: R20.2, U5.7
unnamed: R22.1, U9.2, U12.13
unnamed: R23.2, U12.8
unnamed: U1.6, U1.7
unnamed: U1.2, U1.11, U1.14, U4.2
unnamed: U2.1, U4.3
unnamed: U10.2, U12.12
unnamed: U11.2, U12.11
VCC: C13.1, U3.12, U3.14, U7.13
VDD: C12.1, U3.6, U3.9, U3.10, U7.14
